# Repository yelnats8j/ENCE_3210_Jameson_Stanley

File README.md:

# ENCE_3210_Jameson_Stanley
Microprocessor Systems 1

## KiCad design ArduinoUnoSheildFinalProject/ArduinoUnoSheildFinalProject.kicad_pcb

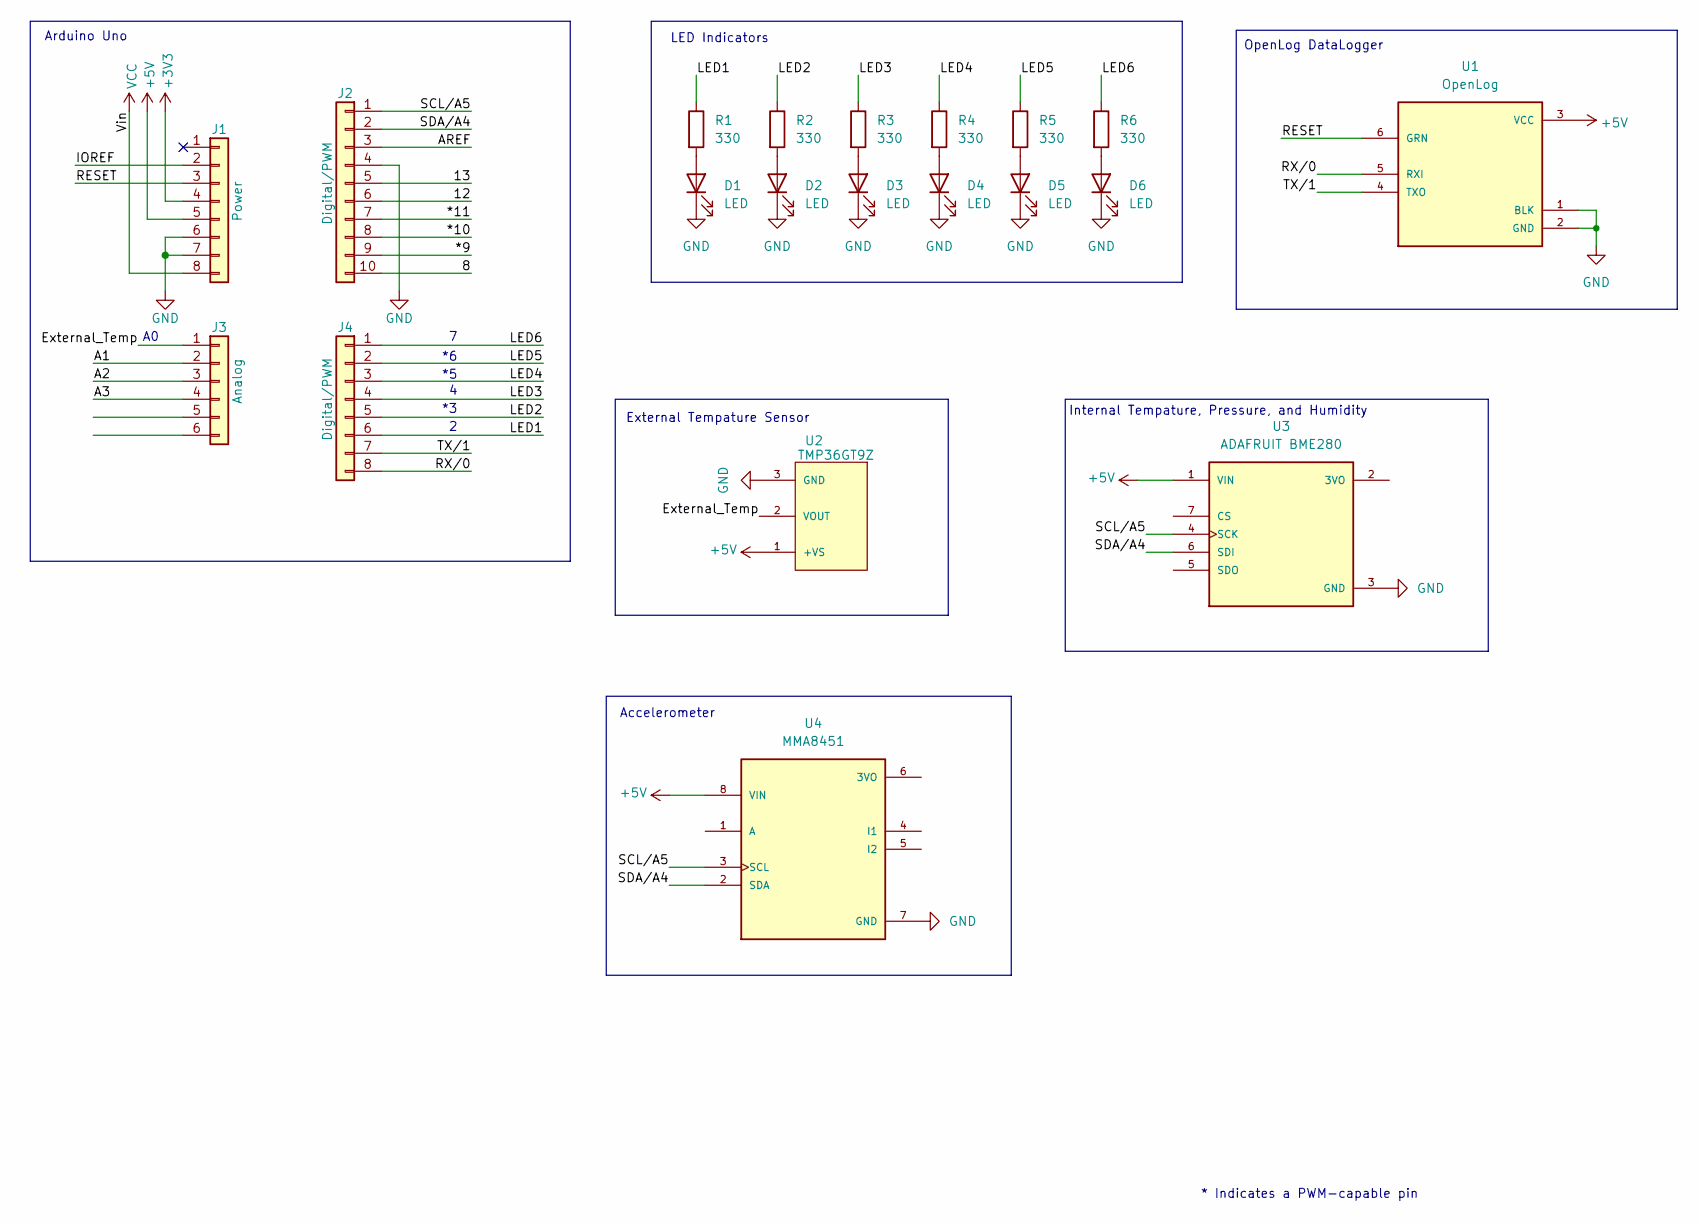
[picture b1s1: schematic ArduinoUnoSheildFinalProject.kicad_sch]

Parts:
D1, D2, D3, D4, D5, D6: LED; LED_D5.0mm
J1: Power; PinSocket_1x08_P2.54mm_Vertical
J2: Digital/PWM; PinSocket_1x10_P2.54mm_Vertical
J3: Analog; PinSocket_1x06_P2.54mm_Vertical
J4: Digital/PWM; PinSocket_1x08_P2.54mm_Vertical
R1, R2, R3, R4, R5, R6: 330; R_Axial_DIN0204_L3.6mm_D1.6mm_P5.08mm_Horizontal
U1: OpenLog; MODULE_DEV-13712; PARTREV v15
U2: TMP36GT9Z; TO92127P521H733-3; PARTREV H
U3: ADAFRUIT BME280; MODULE_2652; PARTREV N/A
U4: MMA8451; MODULE_2019; PARTREV 2021-11-15

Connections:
+3V3: J1.4
+5V: J1.5, U1.3 (VCC), U2.1 (+VS), U3.1 (VIN), U4.8 (VIN)
/8: J2.10
/12: J2.6
/13: J2.5
/*9: J2.9
/*10: J2.8
/*11: J2.7
/A1: J3.2
/A2: J3.3
/A3: J3.4
/AREF: J2.3
/External_Temp: J3.1, U2.2 (VOUT)
/IOREF: J1.2
/LED1: J4.6, R1.1
/LED2: J4.5, R2.1
/LED3: J4.4, R3.1
/LED4: J4.3, R4.1
/LED5: J4.2, R5.1
/LED6: J4.1, R6.1
/RESET: J1.3, U1.6 (GRN)
/RX/0: J4.8, U1.5 (RXI)
/SCL/A5: J2.1, U3.4 (SCK), U4.3 (SCL)
/SDA/A4: J2.2, U3.6 (SDI), U4.2 (SDA)
/TX/1: J4.7, U1.4 (TXO)
GND: D1.1 (K), D2.1 (K), D3.1 (K), D4.1 (K), D5.1 (K), D6.1 (K), J1.6, J1.7, J2.4, U1.1 (BLK), U1.2 (GND), U2.3 (GND), U3.3 (GND), U4.7 (GND)
unnamed: D1.2 (A), R1.2
unnamed: D2.2 (A), R2.2
unnamed: D3.2 (A), R3.2
unnamed: D4.2 (A), R4.2
unnamed: D5.2 (A), R5.2
unnamed: D6.2 (A), R6.2
VCC: J1.8

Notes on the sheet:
Internal Tempature, Pressure, and Humidity
Accelerometer
OpenLog DataLogger
Arduino Uno
* Indicates a PWM-capable pin
External Tempature Sensor
LED Indicators

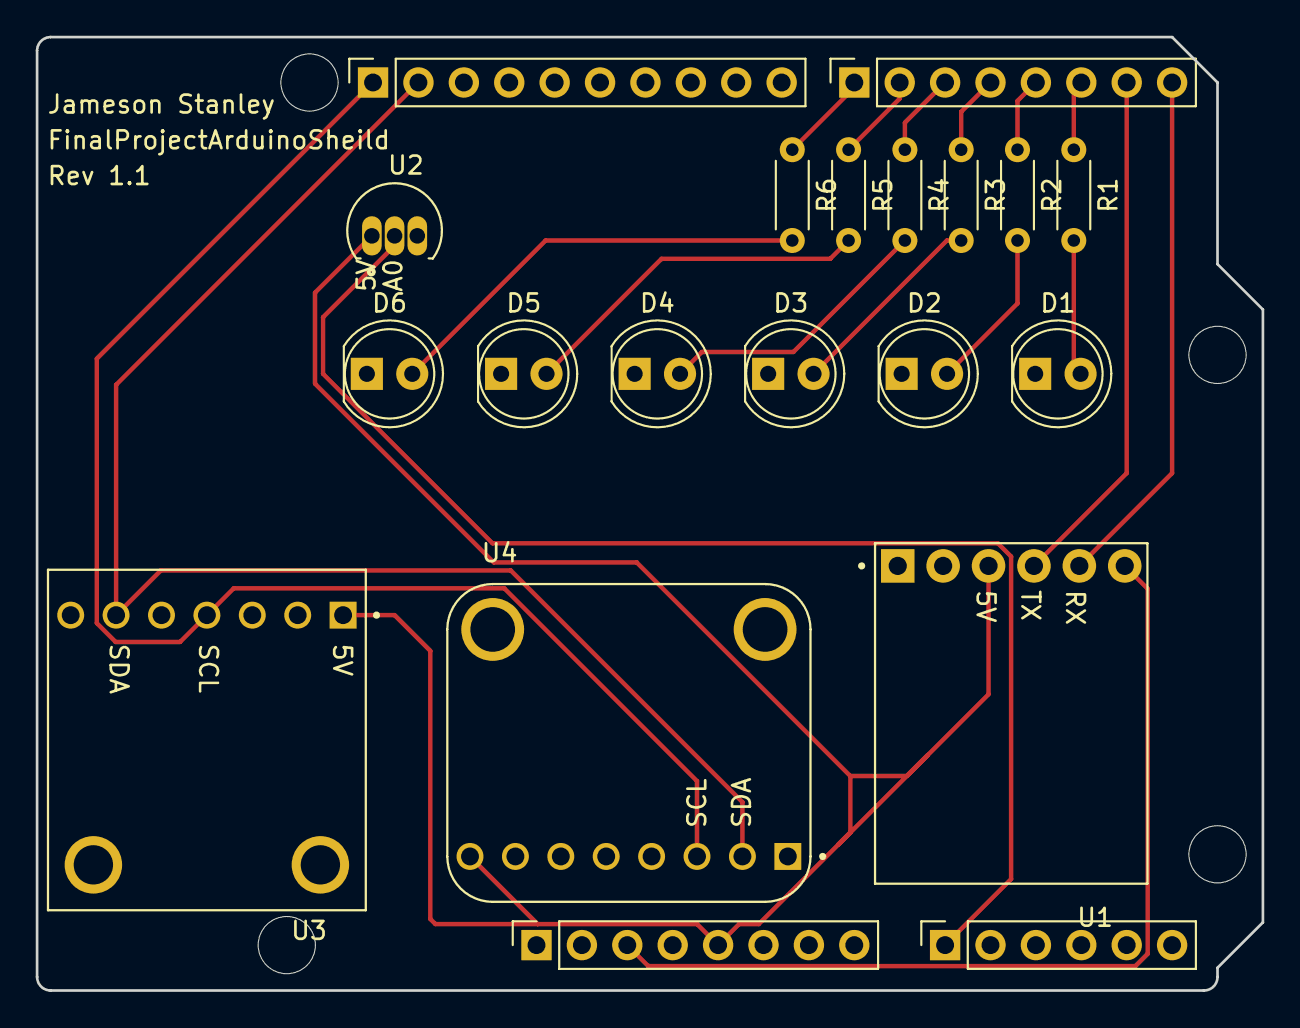
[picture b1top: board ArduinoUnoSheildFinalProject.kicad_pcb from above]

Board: 2 copper layers, 68.6 x 53.3 mm, 24 parts (0 on the bottom side), 20 nets.

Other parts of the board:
MH1, MH2, MH3, MH4: MountingHole_3.2mm

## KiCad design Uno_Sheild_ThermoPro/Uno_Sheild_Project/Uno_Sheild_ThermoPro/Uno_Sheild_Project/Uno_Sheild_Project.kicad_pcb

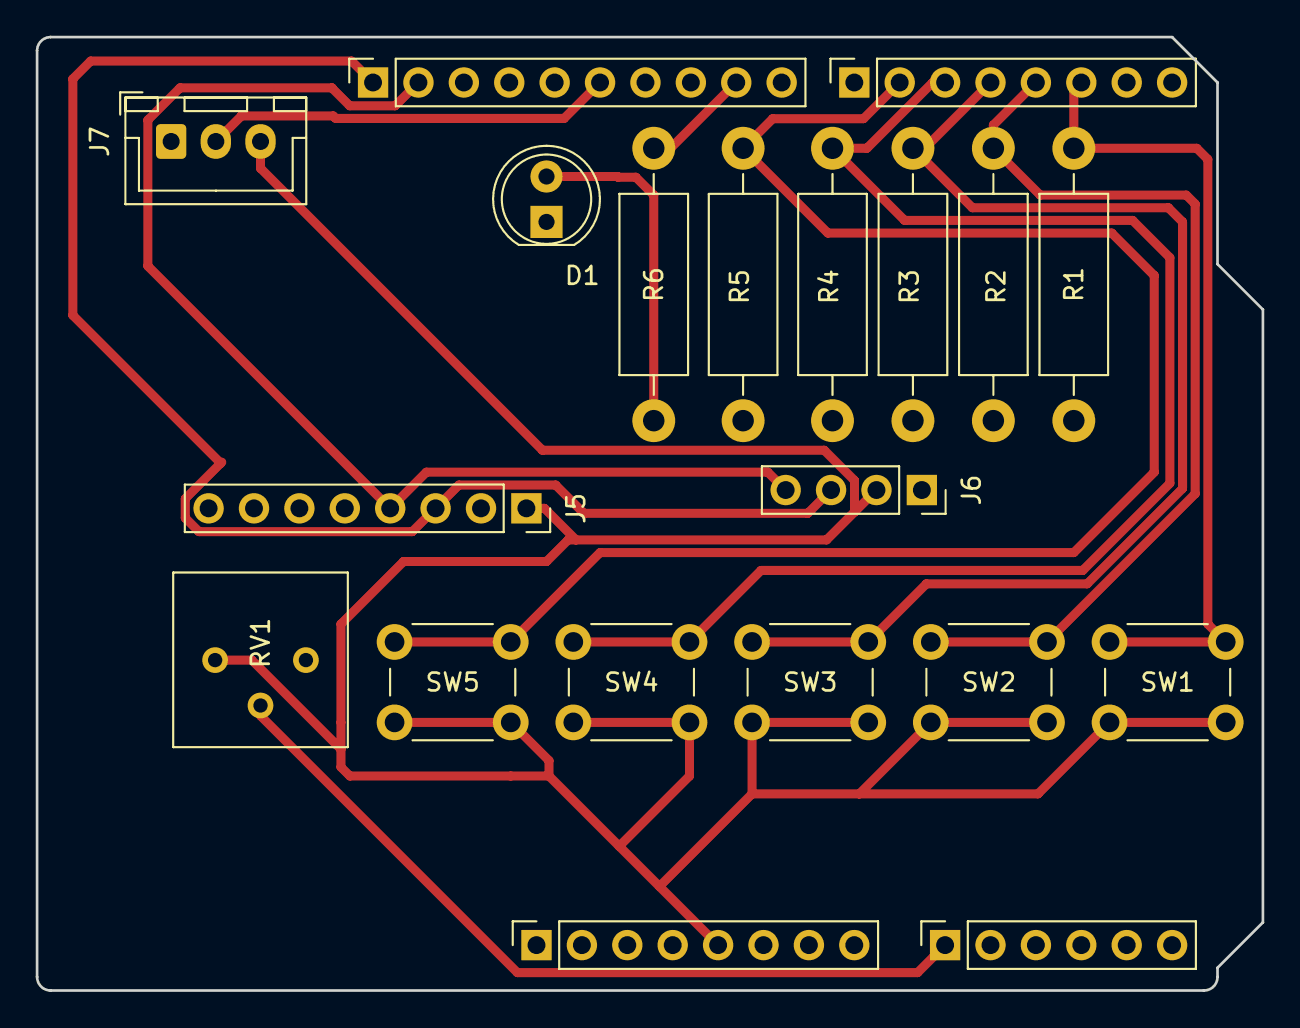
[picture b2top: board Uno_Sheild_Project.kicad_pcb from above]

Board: 2 copper layers, 68.6 x 53.3 mm, 20 parts (0 on the bottom side), 13 nets.

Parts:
D1: LED; LED_D5.0mm
J1: Power; PinSocket_1x08_P2.54mm_Vertical
J2: Digital/PWM; PinSocket_1x10_P2.54mm_Vertical
J3: Analog; PinSocket_1x06_P2.54mm_Vertical
J4: Digital/PWM; PinSocket_1x08_P2.54mm_Vertical
J5: CONN_GYRO; PinSocket_1x08_P2.54mm_Vertical
J6: CONN_DISPLAY; PinSocket_1x04_P2.54mm_Vertical
J7: Conn_01x03; JST_XH_B3B-XH-A_1x03_P2.50mm_Vertical
R1, R2, R3, R4, R5: 100k; R_Axial_DIN0411_L9.9mm_D3.6mm_P15.24mm_Horizontal
R6: 1k; R_Axial_DIN0411_L9.9mm_D3.6mm_P15.24mm_Horizontal
RV1: 10k; Potentiometer_Bourns_3386P_Vertical
SW1, SW2, SW3, SW4, SW5: SW_SPST; SW_PUSH_6mm

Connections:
+5V: J1.5, J5.1, J6.2, J7.3, RV1.1, SW1.2 (B), SW2.2 (B), SW3.2 (B), SW4.2 (B), SW5.2 (B)
/I2C_SCL: J2.1, J5.3, J6.3
/I2C_SDA: J2.2, J5.4, J6.4
/button_cal: J4.3, R4.1, SW4.1 (A)
/button_light: J4.4, R3.1, SW3.1 (A)
/button_lock: J4.2, R5.1, SW5.1 (A)
/button_onoff: J4.6, R1.1, SW1.1 (A)
/button_units: J4.5, R2.1, SW2.1 (A)
/led_light: J2.9, R6.1
/temp_digital: J2.6, J7.2
/temp_sensor: J3.1, RV1.2
GND: D1.1 (K), J1.6, J1.7, J2.4, J5.2, J6.1, J7.1, R1.2, R2.2, R3.2, R4.2, R5.2, RV1.3
unnamed: D1.2 (A), R6.2

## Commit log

2025-01-23 Lab_02
